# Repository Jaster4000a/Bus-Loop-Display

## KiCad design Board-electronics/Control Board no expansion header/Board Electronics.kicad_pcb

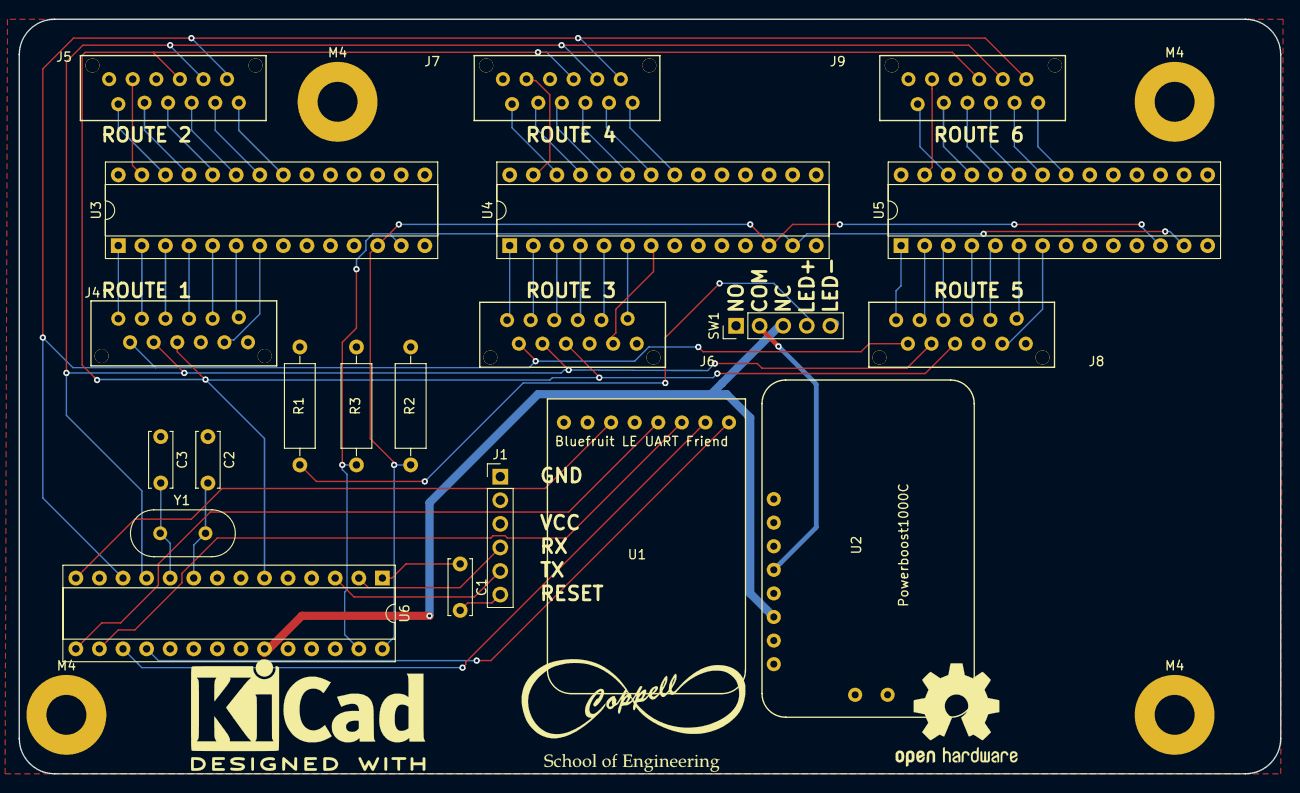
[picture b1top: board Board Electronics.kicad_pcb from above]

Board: 2 copper layers, 135.9 x 81.3 mm, 25 parts (0 on the bottom side), 63 nets.

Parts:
C1: C.1uF; C_Disc_D6.0mm_W2.5mm_P5.00mm
C2, C3: C20p; C_Disc_D6.0mm_W2.5mm_P5.00mm
J1: CONN_01X06; Pin_Header_Straight_1x06_Pitch2.54mm
J4, J5, J6, J7, J8, J9: CONN_02X06; Picofit-12
M4, M4#2, M4#3, M4#4: MountingHole_4.3mm_M4_Pad
R1: R220; R_Axial_DIN0309_L9.0mm_D3.2mm_P12.70mm_Horizontal
R2, R3: R4K7; R_Axial_DIN0309_L9.0mm_D3.2mm_P12.70mm_Horizontal
SW1: SW_SPDT_LED; Pin_Header_Straight_1x05_Pitch2.54mm
U1: Adafruit_Bluefruit_LE_UART_Friend; Blueferuit_LE_UART
U2: Powerboost1000C; Powerboost1000c
U3, U4, U5: MCP23017; DIP-28_W7.62mm_Socket
U6: ATMEGA328P-PU; DIP-28_W7.62mm_Socket
Y1: Crystal; Crystal_HC49-U_Vertical

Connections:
/CKA: J4.5, J5.5, J6.5, J7.5, J8.5, J9.5, U6.6
/CKB: J4.3, J5.3, J6.3, J7.3, J8.3, J9.3, U6.11
/CKC: J4.1, J5.1, J6.1, J7.1, J8.1, J9.1, U6.12
/CTS: U1.2, U6.17
/GND: C2.1, C3.1, J1.1, J4.7, J5.7, J6.7, J7.7, J8.7, J9.7, SW1.1, SW1.5, U1.7, U2.7, U3.10, U3.15, U3.16, U3.17, U4.10, U4.16, U4.17, U5.10, U5.16, U5.17, U6.8, U6.22
/MOD: U1.1, U6.18
/RST: C1.2, J1.6
/RTS: U1.6, U6.14
/RX: J1.4, U6.2
/RXI: U1.4, U6.15
/SCL: R2.1, U3.12, U4.12, U5.12, U6.28
/SDA: R3.1, U3.13, U4.13, U5.13, U6.27
/TX: J1.5, U6.3
/TXO: U1.3, U6.16
/VCC: J1.3, R1.2, R2.2, R3.2, U1.5, U2.8, U3.9, U3.18, U4.9, U4.15, U4.18, U5.9, U5.15, U5.18, U6.7, U6.20
/controller.sch/A0: SW1.3, U2.6, U6.23
/controller.sch/RESET: C1.1, U6.1
unnamed: C2.2, U6.9, Y1.1
unnamed: C3.2, U6.10, Y1.2
unnamed: J4.2, U3.1
unnamed: J4.4, U3.2
unnamed: J4.6, U3.3
unnamed: J4.8, U3.4
unnamed: J4.9, U3.7
unnamed: J4.10, U3.5
unnamed: J4.12, U3.6
unnamed: J5.2, U3.21
unnamed: J5.4, U3.22
unnamed: J5.6, U3.23
unnamed: J5.8, U3.24
unnamed: J5.9, U3.27
unnamed: J5.10, U3.25
unnamed: J5.12, U3.26
unnamed: J6.2, U4.1
unnamed: J6.4, U4.2
unnamed: J6.6, U4.3
unnamed: J6.8, U4.4
unnamed: J6.9, U4.7
unnamed: J6.10, U4.5
unnamed: J6.12, U4.6
unnamed: J7.2, U4.21
unnamed: J7.4, U4.22
unnamed: J7.6, U4.23
unnamed: J7.8, U4.24
unnamed: J7.9, U4.27
unnamed: J7.10, U4.25
unnamed: J7.12, U4.26
unnamed: J8.2, U5.1
unnamed: J8.4, U5.2
unnamed: J8.6, U5.3
unnamed: J8.8, U5.4
unnamed: J8.9, U5.7
unnamed: J8.10, U5.5
unnamed: J8.12, U5.6
unnamed: J9.2, U5.21
unnamed: J9.4, U5.22
unnamed: J9.6, U5.23
unnamed: J9.8, U5.24
unnamed: J9.9, U5.27
unnamed: J9.10, U5.25
unnamed: J9.12, U5.26
unnamed: R1.1, SW1.4
unnamed: SW1.2, U2.4

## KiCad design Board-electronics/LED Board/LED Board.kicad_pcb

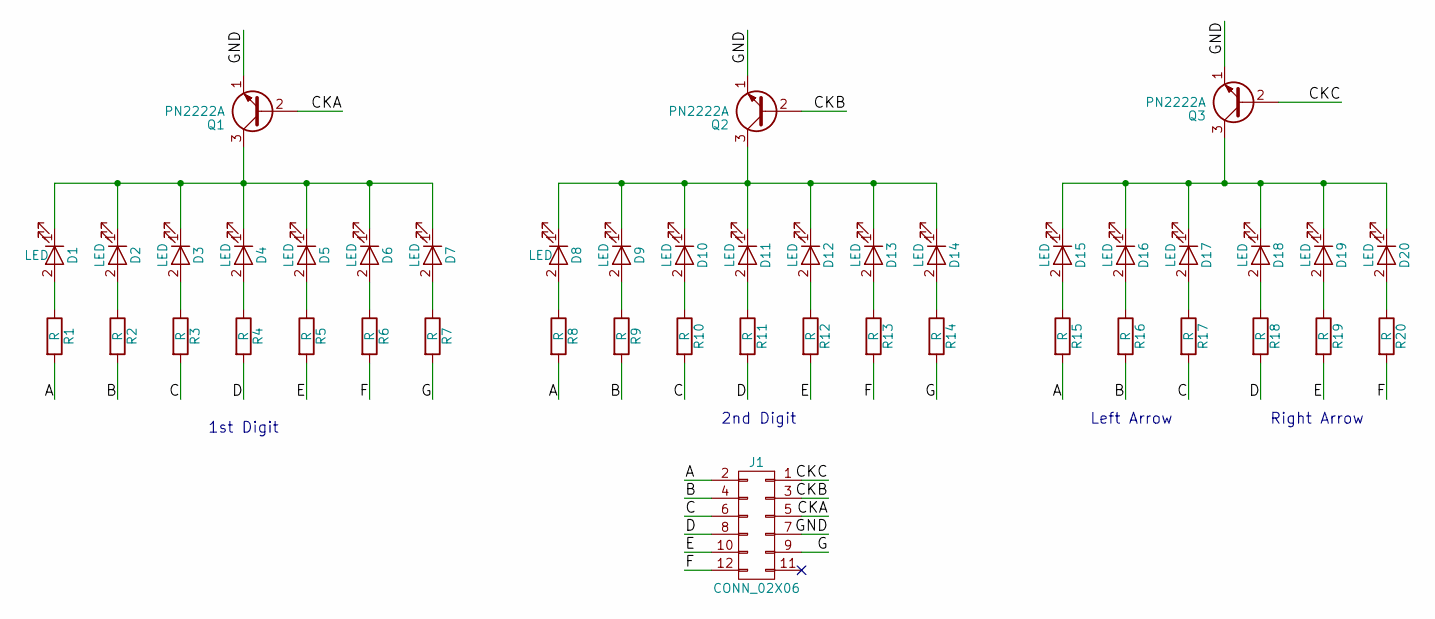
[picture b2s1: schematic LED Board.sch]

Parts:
D1, D2, D3, D4, D5, D6, D7, D8, D9, D10, D11, D12, D13, D14, D15, D16, D17, D18, D19, D20: LED; LED_D5.0mm
J1: CONN_02X06; Picofit-12
Q1, Q2, Q3: PN2222A; TO-92_Molded_Narrow
R1, R2, R3, R4, R5, R6, R7, R8, R9, R10, R11, R12, R13, R14, R15, R16, R17, R18, R19, R20: R; R_Axial_DIN0207_L6.3mm_D2.5mm_P10.16mm_Horizontal

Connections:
/A: J1.2, R1.2, R8.2, R15.2
/B: J1.4, R2.2, R9.2, R16.2
/C: J1.6, R3.2, R10.2, R17.2
/CKA: J1.5, Q1.2 (B)
/CKB: J1.3, Q2.2 (B)
/CKC: J1.1, Q3.2 (B)
/D: J1.8, R4.2, R11.2, R18.2
/E: J1.10, R5.2, R12.2, R19.2
/F: J1.12, R6.2, R13.2, R20.2
/G: J1.9, R7.2, R14.2
/GND: J1.7, Q1.1 (E), Q2.1 (E), Q3.1 (E)
unnamed: D1.1 (K), D2.1 (K), D3.1 (K), D4.1 (K), D5.1 (K), D6.1 (K), D7.1 (K), Q1.3 (C)
unnamed: D1.2 (A), R1.1
unnamed: D2.2 (A), R2.1
unnamed: D3.2 (A), R3.1
unnamed: D4.2 (A), R4.1
unnamed: D5.2 (A), R5.1
unnamed: D6.2 (A), R6.1
unnamed: D7.2 (A), R7.1
unnamed: D8.2 (A), R8.1
unnamed: D9.2 (A), R9.1
unnamed: D8.1 (K), D9.1 (K), D10.1 (K), D11.1 (K), D12.1 (K), D13.1 (K), D14.1 (K), Q2.3 (C)
unnamed: D10.2 (A), R10.1
unnamed: D11.2 (A), R11.1
unnamed: D12.2 (A), R12.1
unnamed: D13.2 (A), R13.1
unnamed: D14.2 (A), R14.1
unnamed: D15.1 (K), D16.1 (K), D17.1 (K), D18.1 (K), D19.1 (K), D20.1 (K), Q3.3 (C)
unnamed: D15.2 (A), R15.1
unnamed: D16.2 (A), R16.1
unnamed: D17.2 (A), R17.1
unnamed: D18.2 (A), R18.1
unnamed: D19.2 (A), R19.1
unnamed: D20.2 (A), R20.1

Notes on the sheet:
1st Digit
2nd Digit
Left Arrow
Right Arrow

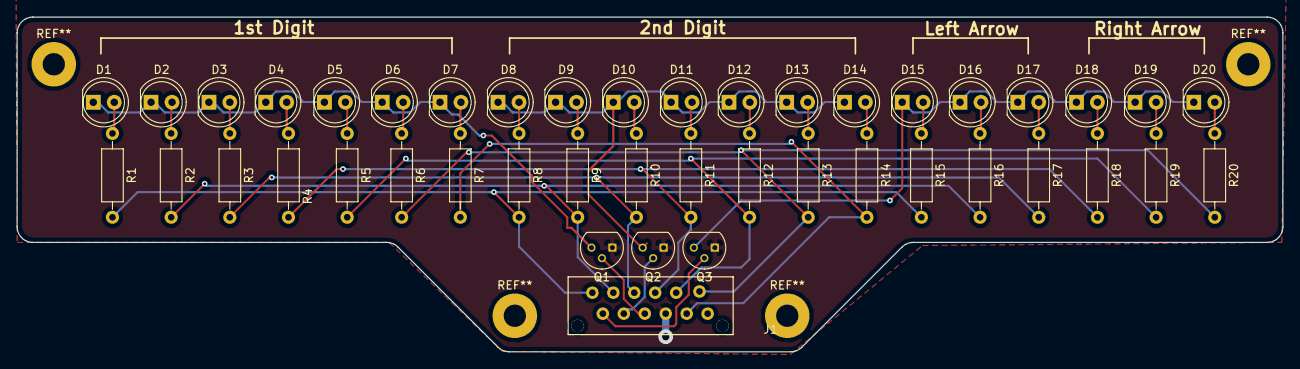
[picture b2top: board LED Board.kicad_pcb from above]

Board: 2 copper layers, 153.4 x 40.6 mm, 44 parts (0 on the bottom side), 34 nets.

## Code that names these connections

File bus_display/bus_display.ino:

#include <Wire.h>             //i2c library, used to talk to MCP23017 Port expanders.
#include <SoftwareSerial.h>   //SoftwareSerial library, allows ATMEGA to talk to bluefruit port over pins other than 0 and 1, allowing for those to remain open for code editing. 

//Libraries used by the bluefruit module, this abstracts away talking to the bluefruit.
#include "Adafruit_BLE.h"
#include "Adafruit_BluefruitLE_UART.h"

#include "BluefruitConfig.h"  //Config file we set up. It should be tab 2 in this program, it contains a few simple settings for the bluefruit



//create bluefruit object. I have inlcuded HWSERIAL and SSERIAL Versions, Use comments to chose the mode you want.
//Software Serial allows for use while device is connected to computer over pins 0 and 1
//Hardware Serial is a bit more reliable
//adafruit says with the flow control pins, software serial is pretty reliable.


//Sofware Serial
SoftwareSerial bluefruitSS = SoftwareSerial(BLUEFRUIT_SWUART_TXD_PIN, BLUEFRUIT_SWUART_RXD_PIN); //Creates Software Serial on pins specified in header file


//declares bluetooth obect
Adafruit_BluefruitLE_UART ble(bluefruitSS, BLUEFRUIT_UART_MODE_PIN,
                              BLUEFRUIT_UART_CTS_PIN, BLUEFRUIT_UART_RTS_PIN);

//Hardware Serial
// Adafruit_BluefruitLE_UART ble(Serial1, BLUEFRUIT_UART_MODE_PIN);


//The digits and Arrows are written in Hex, because that is the most commonly used form for I2C transmission. They break down into binary as instruction on what LED segments should be lit up.
//0    1      2    3     4       5     6    7      8    9     -
const byte digits[] = {0x3f, 0x06, 0x5b, 0x4f, 0x66, 0x6d, 0x7d, 0x07, 0x7f, 0x6f, 0x00};
//off   left  right
const byte arrows[] = {0x07, 0x38};
//  1     2     3
const byte chips[] = {0x20, 0x21, 0x22};
//  A     B
const byte ports[] = {0x14, 0x15};

const int blinkTime = 1000;


float voltage;

byte bank[6][3] = {
  {digits[10], digits[10], digits[10]},  //digit 1
  {digits[10], digits[10], digits[10]},  //digit 2
  {digits[10], digits[10], digits[10]},  //digit 3

  {digits[10], digits[10], digits[10]},  //digit 4
  {digits[10], digits[10], digits[10]},  //digit 5
  {digits[10], digits[10], digits[10]},  //digit 6
};

String data = "";

const byte cka = 4;
const byte ckb = 5;
const byte ckc = 6;
boolean batWarn = false;

void setup() {
  pinMode(cka, OUTPUT);
  pinMode(ckb, OUTPUT);
  pinMode(ckc, OUTPUT);
  digitalWrite(cka, LOW);
  digitalWrite(ckb, LOW);
  digitalWrite(ckc, LOW);
  Wire.begin();         //set up i2c
  Serial.begin(115200); //set serial at 115200 baud, for high speed data transfer
  Serial.println(F("CHS Bus Loop Dispatch System Debug Terminal"));

  //set all pins on our i2c chips to output
  for (int i = 0; i < 3; i++) {
    Wire.beginTransmission(chips[i]);
    Wire.write(0x00);
    Wire.write(0x00);
    Wire.endTransmission();
    Wire.beginTransmission(chips[i]);
    Wire.write(0x01);
    Wire.write(0x00);
    Wire.endTransmission();

  }



  //initalize bluefruit, and select verbosity.
  if (!ble.begin(VERBOSE_MODE)) {
    error(F("Could not find Bluefruit, make it is wired and switch is in CMD"));
  }
  Serial.println( F("BLE Initialized!") );

  delay(1000);
  //if factory reset flagged, resets system
  if (FACTORYRESET_ENABLE) {
    Serial.println(F("Performing Factory Reset"));
    if (!ble.factoryReset()) {
      error(F("Factory Reset Failed, this sometimes happens after uploading code"));
    }
  }
  
  ble.sendCommandCheckOK("AT+GAPDEVNAME=" deviceName);

  ble.echo(false); //disables command echo from Bluefruit, reducing tx/rx times.
  ble.info(); //Display information about bluefruit over serial bus.
  ble.verbose(false); //debug info gets annoying, remove if something is really wonky.



  //Wait for connection
  while (!ble.isConnected()) {
    delay(500);
  }

  //set up LED mode. this is only supported on firmware 0.6.6 and up,
  //so we need to check it first

  if (ble.isVersionAtLeast(MINIMUM_FIRMWARE_VERSION)) {
    ble.sendCommandCheckOK("AT+HWModeLED=" MODE_LED_BEHAVIOUR);
    Serial.println(F("set led to " MODE_LED_BEHAVIOUR));
  }


  //Set module to DATA Mode, so the chip acts as a serial passthrough

  Serial.println(F("Switching to DATA Mode"));
  ble.setMode(BLUEFRUIT_MODE_DATA);

}

void loop() {
  if (ble.available()) {
    getMsg();
  }
  digitalWrite(cka, HIGH);
  blinkChips(bank[0][0], bank[1][0], bank[2][0], bank[3][0], bank[4][0], bank[5][0]);
  digitalWrite(cka, LOW);
  digitalWrite(ckb, HIGH);
  blinkChips(bank[0][1], bank[1][1], bank[2][1], bank[3][1], bank[4][1], bank[5][1]);
  digitalWrite(ckb, LOW);
  digitalWrite(ckc, HIGH);
  blinkChips(bank[0][2], bank[1][2], bank[2][2], bank[3][2], bank[4][2], bank[5][2]); //TODO try tweaking this specific line to pass raw value instead of variable.
  digitalWrite(ckc, LOW);
  voltage = analogRead(0);
  voltage = mapFloat(voltage, 0, 1023, 0, 5);
  /* if(voltage < 3.4 && !batWarn){
     ble.print(F("Low Battery"));
     batWarn = true;
    }*/
}

void splitMsg(String msg) {
  //split message into 2 longs, so it can hold this data
  unsigned long first = msg.substring(0, 9).toInt();
  unsigned long last = msg.substring(9).toInt();
  //write values to bank using first and last variables
  unsigned long divisor = 100000000;                                     //set a divisor to find the first digit
  for (int x = 0; x < 3; x++) {                                           //loop through the first three banks
    for (int y = 0; y < 3; y++) {                                         //loop through the three digits per bank
      if (y == 2) {
        bank[x][y] = arrows[(first / divisor) % 10];

      } else {
        bank[x][y] = digits[(first / divisor) % 10];                        //find the value that should go in this digit
      }
      divisor = divisor / 10;                                             //divide the divisor, so next time we get the next digit.
    }
  }
  //do the same as above, but with the last three banks
  divisor = 100000000;
  for (int x = 3; x < 6; x++) {
    for (int y = 0; y < 3; y++) {
      if (y == 2) {
        bank[x][y] = arrows[(last / divisor) % 10];
      } else {
        bank[x][y] = digits[(last / divisor) % 10];
      }
      divisor = divisor / 10;
    }
  }
  for (int i = 0; i < 6; i++) {
    for (int q = 0; q < 3; q++) {

      Serial.print(bank[i][q], HEX);
      Serial.print("  ");
      if (q == 2) {
        Serial.println("");
      }
    }
  }

}



void getMsg() {
  data = "";
  while (ble.available()) {
    int c = ble.read();
    data.concat((char)c);
  }
  splitMsg(data);

}

void blinkChips(byte a1, byte b1, byte a2, byte b2, byte a3, byte b3) {
  writeChip(chips[0], ports[0], a1);
  writeChip(chips[1], ports[0], a2);
  writeChip(chips[2], ports[0], a3);
  delayMicroseconds(blinkTime);
  writeChip(chips[0], ports[0], 0);
  writeChip(chips[1], ports[0], 0);
  writeChip(chips[2], ports[0], 0);

  writeChip(chips[0], ports[1], b1);
  writeChip(chips[1], ports[1], b2);
  writeChip(chips[2], ports[1], b3);
  delayMicroseconds(blinkTime);
  writeChip(chips[0], ports[1], 0);
  writeChip(chips[1], ports[1], 0);
  writeChip(chips[2], ports[1], 0);

}

void writeChip(byte chip, byte reg, byte data) {
  Wire.beginTransmission(chip);
  Wire.write(reg);
  Wire.write(data);
  Wire.endTransmission();
}

// A small helper for throwing initialization errors.

void error(const __FlashStringHelper*err) {
  Serial.println(err);
  while (1);
}

float mapFloat(long x, long in_min, long in_max, long out_min, long out_max)
{
  return (float)(x - in_min) * (out_max - out_min) / (float)(in_max - in_min) + out_min;
}

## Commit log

2017-05-30 Keyboard, TableView, Cell Tap
    Keyboard dismisses when clicking out, so does cell tap, Tableview
    displays all BLE devices
2017-05-31 May 31
    Nothing new really, just attempting to get it to go back to connect to
    an old peripheral
2017-06-01 Failed attempt at tableview bluetooth sync
    Tried, syncing tableview and bluetooth but nothing yet
